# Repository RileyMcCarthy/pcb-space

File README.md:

# pcb-space

**Zener (`pcb`) is the netlist language and PCB seeder. pcb-space owns the schematic drawing, place, route, and fab.**

This is not a Zener fork. You write a `.zen` board and a `.place.py`. **`pcb-space build` is the compiler:** schematic (`pcb build` + lint) → seed (`pcb layout --no-open`) → place → route → fab. The agent never has to click Pcbnew.

```
pcb-space source   MPN / LCSC → Zener package + SOURCE.json
      ↓
.zen + .place.py   intent (Zener nets, CSS locks, NetReq)
      ↓
pcb-space schematic   default.net → .kicad_sch (readable drawing)
pcb-space build       seed → place → route → fab
```

Already-committed `placed/` / `routed/` / `fab/` are left alone. `--force` or `--from place` is an opt-in rebuild (a new PCBA). `pcb layout` on those directories duplicates footprints; `seed` / `place` / `build` refuse them.

## Getting started

You need four tools on `PATH`:

| Tool | Role |
|---|---|
| [`pcb`](https://github.com/diodeinc/pcb) (Zener) | Schematic, `pcb build`, `pcb layout --no-open` |
| `pcb-space` | Place, route, silk, fab, source, status |
| KiCad 10 `kicad-cli` | DRC, Gerbers, review SVGs |
| KiCadRoutingTools (`KRT_HOME`, default `~/Downloads/KiCadRoutingTools`) | Place legalize + route engine |

```bash
pip install -e ".[dev]"          # this repo
# pcb: https://github.com/diodeinc/pcb  → ~/.local/bin/pcb
# KiCad 10: macOS app, or Ubuntu ppa:kicad/kicad-10.0-releases
export KRT_HOME=~/Downloads/KiCadRoutingTools

pcb-space init blinky -C ./blinky
# source parts, write the .zen and Place() locks, then:
pcb-space build blinky.place.py
pcb-space status blinky.place.py
```

`--upto schematic|seed|place|route|fab` stops early. `--dry-run` prints the plan. `--force` rebuilds from schematic (new copper).

Worked PCBA (already fabbed in git — `build` is a no-op until `--force`):

```bash
pcb-space build   examples/c3_usb --dry-run
pcb-space status  examples/c3_usb
pcb-space lint    examples/c3_usb/c3_usb.zen
```

## Why this exists

KiCad 10 already *uses* 0.20 mm traces and *checks* clearance. It will not:

- derive 0.20/0.15 mm from “USB 2.0, 90 Ω” plus a JLCPCB 4-layer stackup
- keep “USB-C at this end, this offset, for the enclosure” in git
- autoroute from a CLI an agent can call

Zener (`Net`, `Module`, `pcb build`) is required for the netlist. pcb-space **sources** parts (LCSC first; DigiKey/Mouser when API keys exist), gates the land against the datasheet body, and compiles placement/routing. `pcb-space lint` checks USB-C both-orientations / CC Rd / ESP32 D+/D− on the `.zen`.

Analog EMG and switching nodes stay `autoroute=False` until you say otherwise. A maze that “meets 0.2 mm width” can still ruin a boost SW loop.

## Install

```bash
pip install -e ".[dev]"
```

Python 3.11+. Compile / apply / check need no extra Python packages. Zener (`pcb`), KiCad 10, and KRT are required for seed / place / route / fab — see Getting started.

## Place file

Placement uses **CSS names**. Unitless numbers are millimetres. The board is the containing block. Locked parts are `position: absolute`. Footprints have intrinsic size (the courtyard), like an ``. `margin: auto` centers on the free axis. `padding` lives on `Board` / `Region`, not on a part.

```python
Board(width=52, height=30, layers=4, stackup="jlcpcb_4l_1oz")

# Flush to the east end, vertically centered. rotate is pre-layout (PCB, not CSS transform).
Place(
    "U26",
    position="absolute",
    right=0,
    top=0,
    bottom=0,
    margin_top="auto",
    margin_bottom="auto",
    rotate=90,
    locked=True,
    reason="USB-C at pod end",
)

# Same thing as a style string (AIs dump CSS this way).
Place(
    "U28",
    style="position:absolute; top:0; left:0; right:0; margin-left:auto; margin-right:auto",
    locked=True,
    reason="FFC to garment",
)

# Enclosure CAD still wins: at= is the KiCad footprint origin.
Place("U32", at=(26.0, 11.5), side="B", locked=True, reason="PPG optical window")

Keepout(
    "ANTENNA",
    position="absolute",
    bottom=0,
    left=0,
    right=0,
    width=16,
    height=2.8,
    margin_left="auto",
    margin_right="auto",
)

Region("header", top=0, left=0, right=0, height=8, padding=0.5)

NetReq("USB_DP", "USB_DN", kind="usb_hs", z_diff_ohm=90, pair=True)
NetReq("3V3", kind="power", volts=3.3, amps=0.25)
NetReq("CH[1-9]*", kind="analog", max_mm=18, vias=False,
       keep_clear_of="BOOST.BOOST_SW", keep_clear_mm=0.5)
```

`Place` accepts the **Zener instance name** (`J1`) or the KiCad reference (`U3`). pcb-space maps them through the footprint `Path` property (`J1.TYPE_C_…` → `U3`).

The web mapping:

| CSS | pcb-space | Notes |
|---|---|---|
| `position: absolute` | locked mechanical part | Engine must not move it |
| `position: static` | unlocked | Engine packs it later |
| `top` / `right` / `bottom` / `left` / `inset` | same | mm or `%` of the containing block |
| `margin` / `margin-top` / … / `auto` | same | Courtyard-to-edge. `auto` + both edges = center |
| `padding` | `Board` / `Region` only | Shrinks the containing block |
| `width` / `height` | `Keepout` / `Region` | Footprints: courtyard is intrinsic |
| `transform: translateY(-50%)` | same, **layout-affecting** | So the web centering trick actually moves copper |
| `rotate` / `transform: rotate(90deg)` | **before** layout | Unlike CSS, rotation changes the used box |
| `at=(x, y)` | KiCad origin | CAD apertures. Do not mix with left/top/right/bottom |
| `side='B'` | back copper | **Not** `z-index` |

Rejected on purpose (clear error, not a silent no-op): `z-index`, `flex` / `grid` / `display:flex`, `px` / `em` / `rem`, `position: sticky|fixed`. Unlocked packing is the engine, not flexbox.

### `NetReq` kinds

| kind | Compiles to | Autoroute |
|---|---|---|
| `usb_hs` | 90 Ω (or `z_diff_ohm`) pair geometry from the stackup | diff pair |
| `power` | IPC-2221 width from `amps` | yes |
| `analog` | F.Cu, no via, length cap | **no** |
| `clock` | length-match group | yes |
| `switch_node` | F.Cu, no via | **no** |
| `digital` | default class | yes |

## Source (parts)

Distributors are not CAD libraries. `source search` lists LCSC/JLC hits — **import does not autoselect EasyEDA.** Pass `--pick C…` when several rows match. ICs need `--footprint` (KiCad land) or opt-in `--easyeda` (graphics + pad numbers). Pin **names** live in the `.zen` definition (board mode, e.g. dual H-bridge). Optional `--pins` JSON only seeds that definition. Passives stay stdlib generics.

```bash
pcb-space source search TPS61023DRLR --fab jlcpcb
pcb-space source import  "100nF 0402" --kind generic -o components
pcb-space source import  C919459 --footprint path/to.kicad_mod --body 1.5x1.5
pcb-space source check   components/Sensirion/SHT40-AD1B --body 1.5x1.5
```

Worked example: `examples/c3_usb/` (USB-C ESP32-C3 node). EasyEDA’s ESP32 land failed the 16.6×13.2 mm body gate; the KiCad MINI-1 land passed.

`pcb-source` is the same commands without the `source` prefix. DigiKey/Mouser rows appear once `DIGIKEY_CLIENT_ID` / `MOUSER_API_KEY` are set; without keys they are listed as skipped, not invented.

## Commands

```bash
pcb-space init    blinky -C ./blinky
pcb-space build   examples/c3_usb --dry-run
pcb-space build   blinky.place.py --upto place
pcb-space lint    examples/c3_usb/c3_usb.zen
pcb-space seed    examples/c3_usb/c3_usb.place.py   # pcb layout --no-open; seed only
pcb-space status  examples/c3_usb
pcb-space refs    examples/c3_usb/c3_usb.place.py
pcb-space nets    examples/c3_usb/c3_usb.place.py --stub
pcb-space compile examples/blinky.place.py
pcb-space apply   examples/blinky.place.py --pcb path/to/layout.kicad_pcb
pcb-space place   examples/c3_usb/c3_usb.place.py
pcb-space check   examples/c3_usb/c3_usb.place.py --pcb path/to/layout_placed.kicad_pcb
pcb-space route   examples/blinky.place.py --pcb path/to/layout.kicad_pcb
pcb-space silk    examples/c3_usb/c3_usb.place.py
pcb-space fab     examples/c3_usb/c3_usb.place.py
pcb-space review  examples/c3_usb/c3_usb.place.py
pcb-space source  search "100nF 0402"
```

Worked PCBA: `examples/c3_usb/` (USB-C → AP2112 → ESP32-C3-MINI-1). CI job `pytest` runs every test except those marked `kicad`. Job `c3-usb-fab` installs KiCad 10 and fabs the committed routed board. Job `krt-4layer` pins KiCadRoutingTools and `place`+`route`+`fab`s `examples/buck_sw/` (4-layer, switch-node cluster).

`apply` locks `Place(..., locked=True)` footprints, writes the `Edge.Cuts` outline from `Board` size when the seed has none, writes net classes into the sibling `.kicad_pro`, writes `.kicad_dru`, and inserts keepout zones. It copies the board to `*.kicad_pcb.bak-pcbspace` first.

`build` is the unified compiler. It skips stages that already have artifacts so a committed `routed/` board is what you order. `--force` / `--from` rebuilds on purpose and writes `layout/<name>/pcbspace.lock.json` (pcb-space, `pcb`, kicad-cli, KRT).

`seed` runs `pcb layout --no-open` on the sibling `.zen` and refuses if the target is under `placed/`, `routed/`, or `fab/`, or already has copper.

`place` copies the **seed**, runs `apply` on the copy, compiles a KRT floorplan-intent (locks, edge bands, keepouts), and legalizes unlocked parts with `place_seed --force --anchors-first`. Locked CSS poses are file-locks; the engine must not move them. Output is `placed/layout.kicad_pcb` next to the seed (a second `.kicad_pro` in the seed directory would make `pcb layout` refuse the project). `pcb layout` is seed-only — never a placer. `pcb-space place` on a packed board is an error.

`status` reports the stage (schematic / seeded / placed / routed / fab), whether `pcb build` is green, `lint` failures, missing `Place()` names, and nets with no `NetReq`.

`refs` maps Zener instance names (`R_CC1`) to KiCad references (`R2`) via footprint `Path`.

`check` fails if a locked part moved, a named keepout disappeared, an analog/SW airwire exceeds `NetReq max_mm`, or different-net pads sit closer than the copper floor (0.10 mm 2-layer / 0.16 mm 4-layer). That last gate is how NTC-on-Teensy pin-row shorts fail place, not only KRT.

`route` picks the `placed/` board when it exists, refreshes net classes, routes USB pairs (`route_diff`), then signals. Analog / switch-node nets get an F.Cu-only pass (`--via-cost 100000`) then stay out of the maze. Every maze / plane step passes `--same-net-pad-clearance` (no via-in-pad on 0603s) and compiled `--via-size/--via-drill` (0.45/0.20). USB-C `qfn_fanout --allow-via-in-pad` is the exception (0.25/0.15 underpad). 4-layer boards with a GND plane get a keep-input-copper GND tap pass so HTSSOP PGND pins dog-bone instead of via-in-pad. 2-layer pours GND last and finalizes. Output is `routed/layout.kicad_pcb`. `--script-only` writes the plan without running it. Set `KRT_HOME` if the router is not in `~/Downloads/KiCadRoutingTools`. True 90 Ω USB needs 4-layer; 1.6 mm 2-layer is a tightly-coupled fab-floor pair, not 90 Ω.

`fab` picks `routed/` when it exists, inserts three F.Cu fiducials (skips a corner whose courtyard is occupied), writes JLCPCB `bom.csv` / `cpl.csv` (LCSC from `SOURCE.json`; through-hole without LCSC omitted as hand-solder; grouped designators quoted), Gerbers, drill, and `FAB_NOTES.md`. Via-in-pad on passives or connector mounting pegs **fails**. USB-C underpad is named, not a Standard-fab fail. Copper `kicad-cli` DRC errors fail the command (2-layer floor 0.10 mm, 4-layer JLCPCB 0.127 mm). It does not upload. KiCad 10 is required for DRC/Gerbers.

## What this is not

- Not a fork of [Zener / pcb](https://github.com/diodeinc/pcb) and not a replacement for it. The schematic is Zener. This tool consumes the KiCad board Zener seeded.
- Not Pcbnew. Interactive routing stays in KiCad for leftover analog you want by hand.
- Not an LLM dumping `(segment …)` into the s-expression.
- Not a CSS layout engine. No flex, no grid, no `px`. Locked parts get a CSS **containing block**. Unlocked parts get a placer.

## Status

v0.4: `pcb-space build` is the compiler (schematic → seed → place → route → fab). Zener is required for the netlist. `init`, `status`, `seed`, `refs`, `lint`, `nets`. CSS locks; `place` / `route` / `silk` / `fab` / `review`. CI: `pytest` (no KiCad) + `c3-usb-fab` (full suite + JLC package); both required to merge.

## License

MIT

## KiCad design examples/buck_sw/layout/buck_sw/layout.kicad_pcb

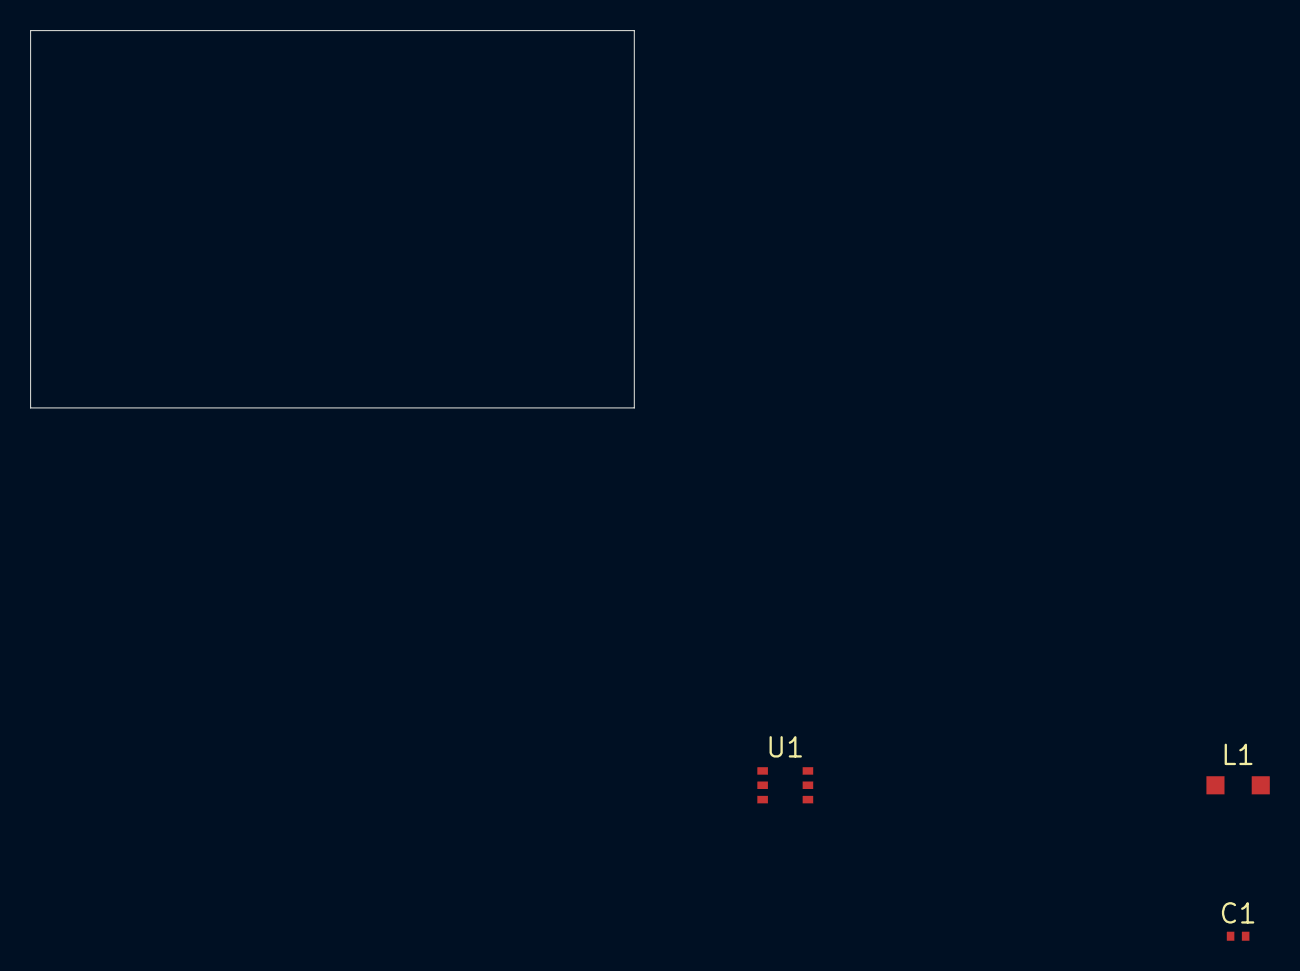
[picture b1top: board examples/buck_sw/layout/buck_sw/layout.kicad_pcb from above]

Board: 4 copper layers, 40.0 x 25.0 mm, 3 parts (0 on the bottom side), 3 nets, no tracks yet.

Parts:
C1: 22uF; C_0402
L1: 15uH; L_4x4
U1: TPS54202; SOT-23-6

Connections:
+5V: C1.1, L1.2
GND: C1.2, U1.1
SW: L1.1, U1.2

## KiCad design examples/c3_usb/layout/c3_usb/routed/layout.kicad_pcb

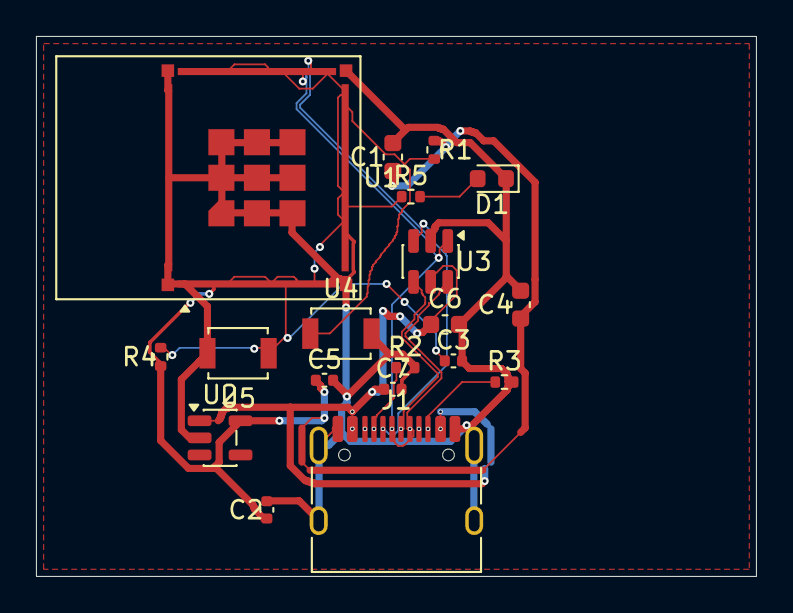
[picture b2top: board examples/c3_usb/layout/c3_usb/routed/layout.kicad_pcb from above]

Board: 2 copper layers, 40.0 x 30.0 mm, 19 parts (0 on the bottom side), 12 nets.

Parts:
C1, C4: CL10A106KP8NNNC; C_0603_1608Metric
C2, C5, C7: CL05B104KO5NNNC; C_0402_1005Metric
C3: CL05A105KA5NQNC; C_0402_1005Metric
C6: CL10A106KO8NQNC; C_0603_1608Metric
D1: KT-0603R; LED_0603_1608Metric
J1: TYPE-C-31-M-12; USB_C_Receptacle_HRO_TYPE-C-31-M-12
R1, R4: 0402WGF1002TCE; R_0402_1005Metric
R2, R3: 0402WGF5101TCE; R_0402_1005Metric
R5: 0402WGF1001TCE; R_0402_1005Metric
U1: ESP32-C3-MINI-1-N4; ESP32-C6-MINI-1
U2: AP2112K-3.3TRG1; SOT-23-5
U3: USBLC6-2SC6; SOT-23-6
U4, U5: B3U-1000P; SW_SPST_B3U-1000P

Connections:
3V3: C1.1, C2.1, C4.1, C5.1, R1.1, R4.1, U1.3, U2.5
BOOT: R1.2, U1.23, U4.1
CC1: J1.A5, R2.1
CC2: J1.B5, R3.1
EN: C3.1, R4.2, U1.8, U5.1
GND: C1.2, C2.2, C3.2, C4.2, C5.2, C6.2, C7.2, D1.1, J1.A1, J1.A12, J1.B1, J1.B12, J1.SH, R2.2, R3.2, U1.1, U1.2, U1.11, U1.14, U1.36, U1.37, U1.38, U1.39, U1.40, U1.41, U1.42, U1.43, U1.44, U1.45, U1.46, U1.47, U1.48, U1.49, U1.50, U1.51, U1.52, U1.53, U2.2, U3.2, U4.2, U5.2
LED: R5.1, U1.16
LED_A: D1.2, R5.2
U1.NC: U1.4, U1.7, U1.9, U1.10, U1.15, U1.17, U1.24, U1.25, U1.28, U1.29, U1.32, U1.33, U1.34, U1.35
USB_DN: J1.A7, J1.B7, U1.26, U3.3, U3.4
USB_DP: J1.A6, J1.B6, U1.27, U3.1, U3.6
VBUS: C6.1, C7.1, J1.A4, J1.A9, J1.B4, J1.B9, U2.1, U3.5
